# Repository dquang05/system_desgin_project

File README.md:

# ESP32 Autonomous Mobile Robot (AMR)

An advanced Autonomous Mobile Robot firmware built on the **ESP-IDF v5.x** framework. Designed with strict real-time constraints, thread-safety, and modular architecture, this project demonstrates professional-grade embedded systems engineering using **FreeRTOS** and Object-Oriented C++.

## 🚀 System Architecture

The firmware is designed with a strict **Application-Library Separation**.

- `lib/`: Contains hardware-agnostic, non-blocking drivers (Motor Control, PID, ADC DMA, Loadcell, Wi-Fi). No FreeRTOS tasks are spawned here.
- `src/`: The Application layer orchestrating high-level state machines, task creation, and global resource management.

### Key Engineering Highlights

- **Deterministic Real-Time Execution:** Motion control and PID loops run precisely at 100Hz in a pinned Core 1 task.
- **Thread Safety:** Lock-free passing where possible, combined with strict `portENTER_CRITICAL` Spinlocks for sharing high-frequency data (like Encoder ticks and ADC raw values) across multicore tasks.
- **Zero Dynamic Allocation in Critical Loops:** No `malloc` or `new` in polling loops. Memory is strictly stack-allocated or statically provisioned at startup to prevent Heap Fragmentation.
- **Direct Memory Access (DMA):** The 5-channel Infrared Line Sensor array is sampled at 20kHz continuously via ESP32's ADC DMA hardware, entirely offloading the CPU.

## 🧠 Control Algorithms

### 1. Velocity Control (Low-Level)

- **Incremental PID Controller:** Controls the TB6612 H-Bridge drivers coupled with Quadrature Encoders.
- **Slew Rate Limiting:** Prevents sudden current spikes (Back-EMF) by artificially capping the maximum acceleration `dv/dt`.
- **Integral Anti-Windup:** Prevents overshooting when wheels are mechanically jammed or lose traction.

### 2. Autonomous Navigation (High-Level)

- **Line Tracking:** Uses Weighted Average (Centroid) calculation with Affine Calibration to determine precise offset error (`e2`).
- **State Machine:** Seamlessly transitions between `MOVING_TO_PICKUP`, `WAITING_FOR_PACKAGE` (Loadcell integration), and `DELIVERING`.
- **Two-Phase Pivot Turn:** Executes precise turning maneuvers at intersections without the need for IMU/Compass, relying purely on encoder odometry and side-sensor polling.

### 3. Remote Telemetry & Tuning

- Utilizes asynchronous **UDP Sockets** to broadcast telemetry data (RPM, Duty Cycle, Sensor Arrays) to a local network at high frequency.
- Supports Live-Tuning: Send a JSON payload via UDP to dynamically update PID gains, steering RPMs, or loadcell thresholds **without recompiling or halting the robot**.

## 🛠️ Build & Flash Instructions

This project is configured using standard ESP-IDF CMake.

1. **Prerequisites:** Ensure ESP-IDF v5.x is installed.
2. **Set Target:**
   ```bash
   idf.py set-target esp32
   ```
3. **Build & Flash:**
   ```bash
   idf.py build
   idf.py -p PORT flash monitor
   ```

## 📁 Repository Structure

```text
├── MCU/
│   ├── include/           # Shared structures, Configs, and Orchestrator Headers
│   ├── src/               # FreeRTOS Tasks (Motion, Telemetry, UDP) & Main
│   ├── lib/               # Independent Component Libraries
│   │   ├── adc_dma/       # Continuous DMA ADC Driver
│   │   ├── loadcell_hx711/# HX711 Weight Sensor
│   │   ├── tb6612_encoder/# Motor & Quadrature Encoder Driver
│   │   ├── velocity_pid/  # Slew-Rate Limited PID
│   │   └── wifi_manager/  # Wi-Fi Station & AP provisioning
│   └── CMakeLists.txt     # Global IDF Component Registration
└── UI/                    # Node.js Server & Web Dashboard for UDP Telemetry
```

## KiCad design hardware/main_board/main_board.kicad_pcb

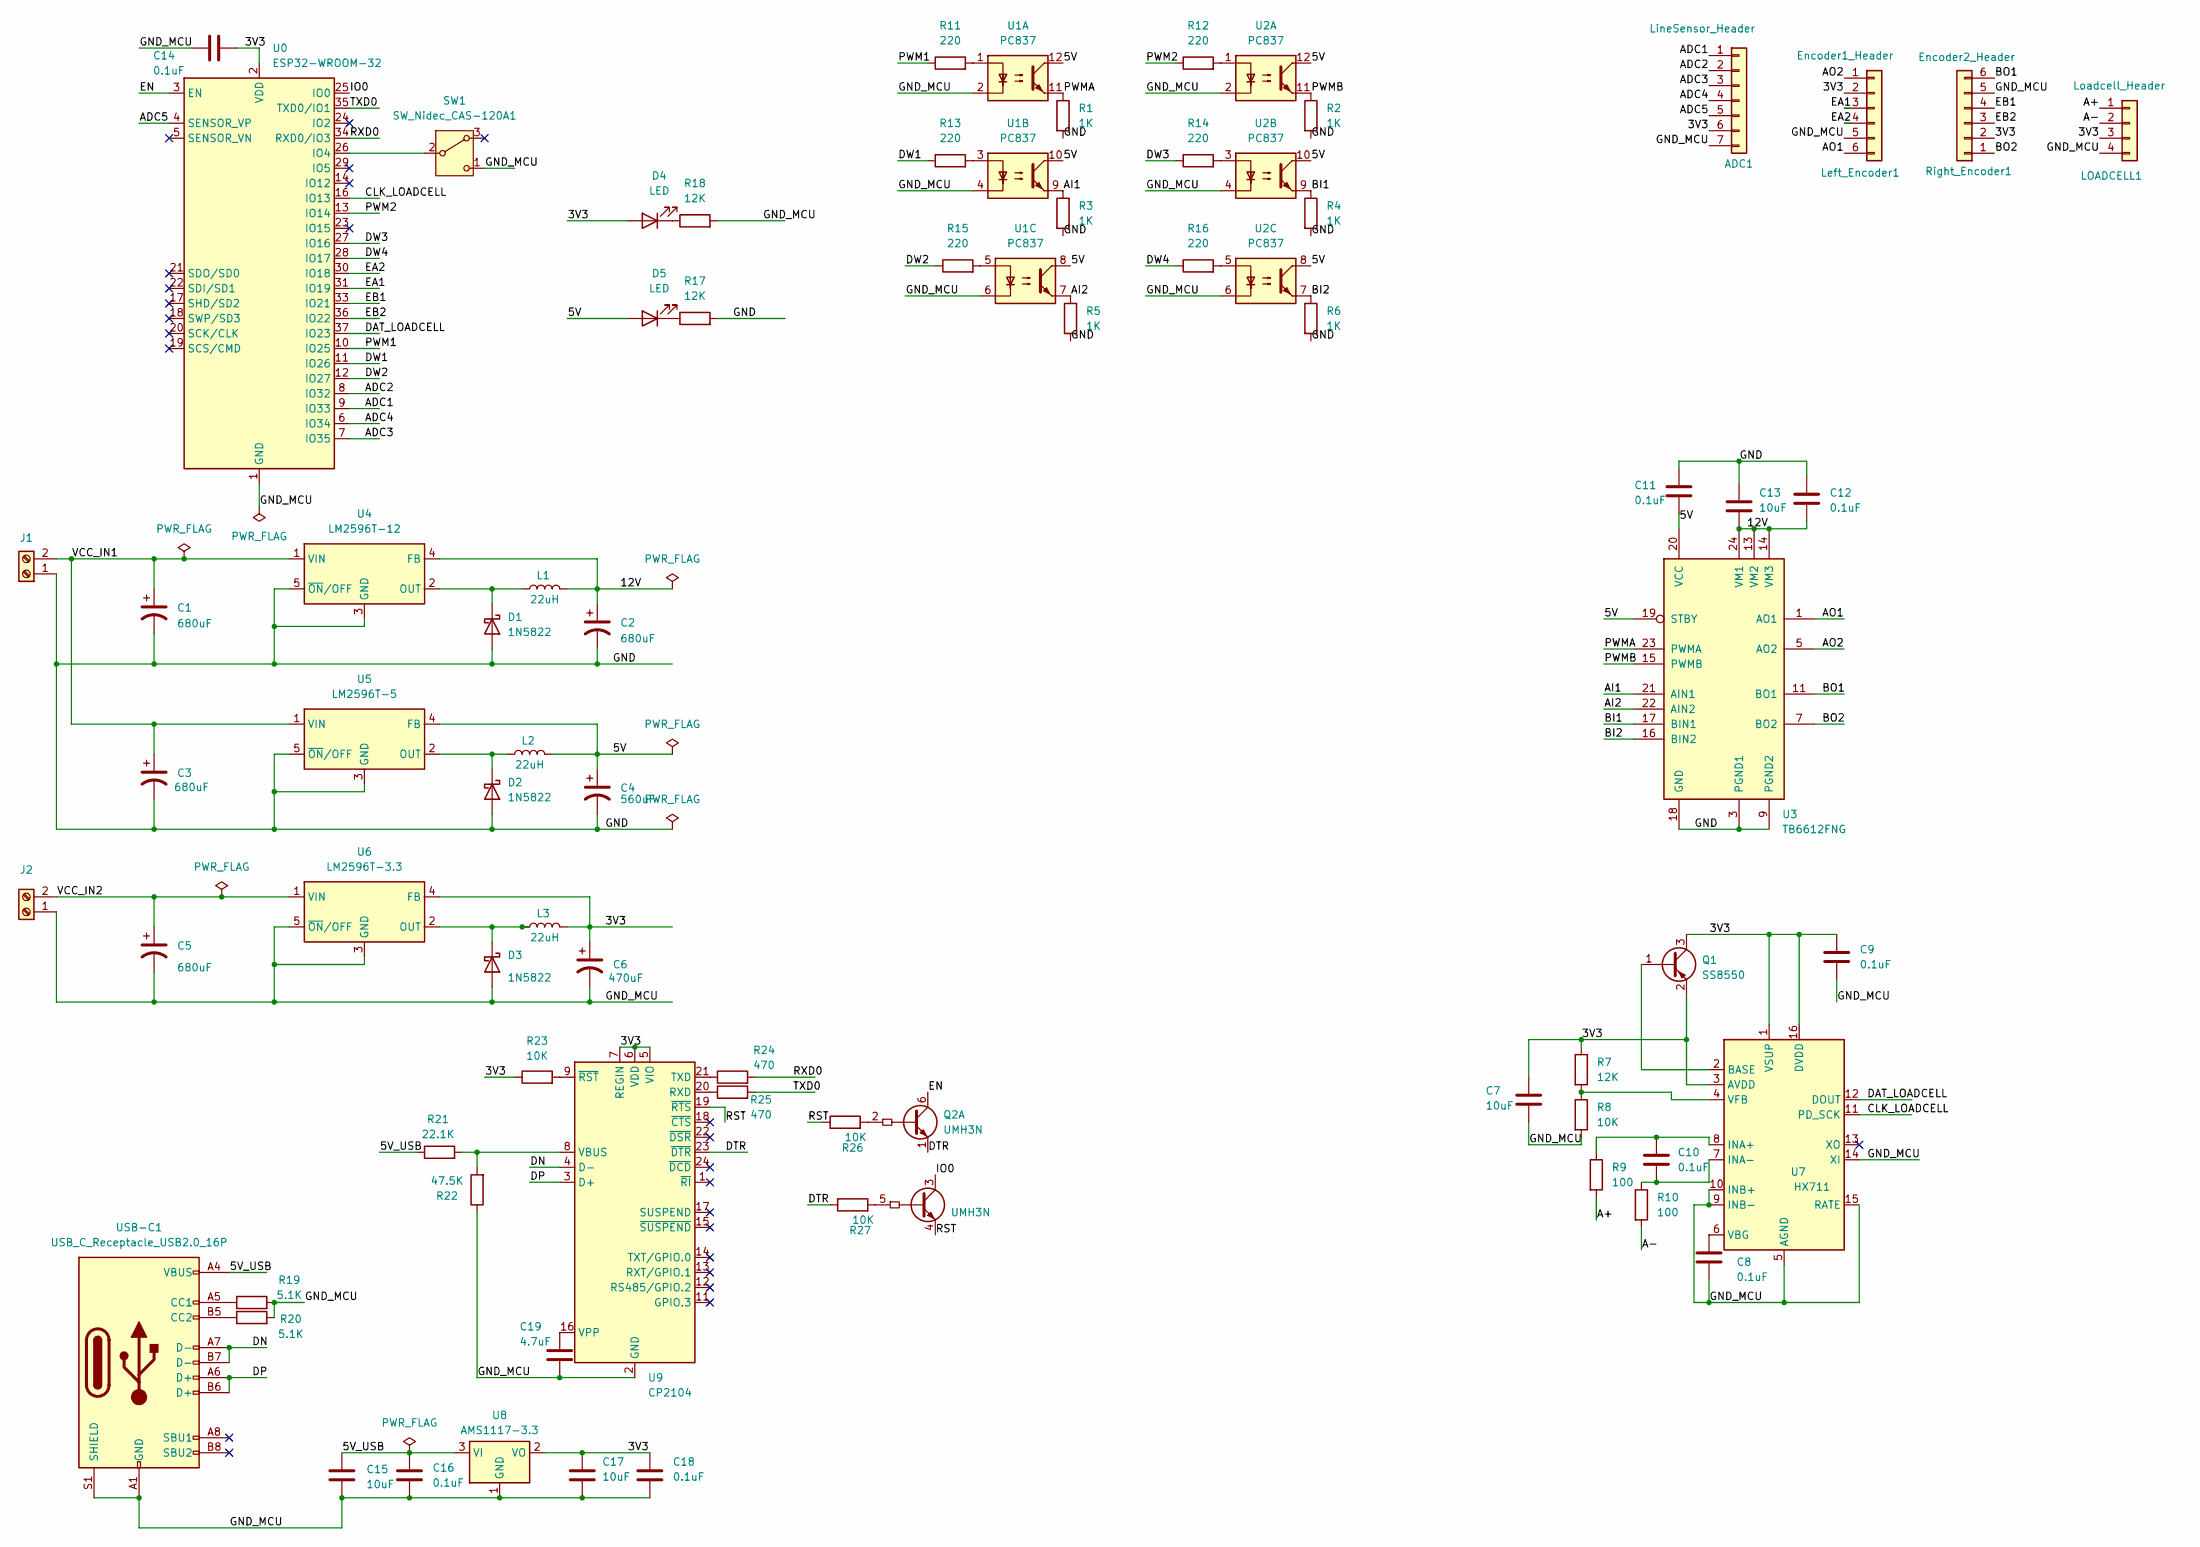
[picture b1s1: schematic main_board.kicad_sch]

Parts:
ADC1: LineSensor_Header; JST_EH_S7B-EH_1x07_P2.50mm_Horizontal
C1, C2, C3, C5: 680uF; CP_Radial_D8.0mm_P5.00mm
C4: 560uF; CP_Radial_D8.0mm_P5.00mm
C6: 470uF; CP_Radial_D8.0mm_P5.00mm
C7, C15, C17: 10uF; C_0805_2012Metric
C8, C9, C10, C11, C12, C14, C16, C18: 0.1uF; C_0805_2012Metric
C13: 10uF; C_1812_4532Metric_Pad1.57x3.40mm_HandSolder
C19: 4.7uF; C_0805_2012Metric
D1, D2, D3: 1N5822; D_0805_2012Metric
D4, D5: LED; LED_0805_2012Metric
J1: MCU POWER; TerminalBlock_bornier-2_P5.08mm
J2: MOTOR POWER; TerminalBlock_bornier-2_P5.08mm
L1, L2, L3: 22uH; L_6.3x6.3_H3
LOADCELL1: Loadcell_Header; JST_EH_S4B-EH_1x04_P2.50mm_Horizontal
Left_Encoder1: Encoder1_Header; JST_EH_S6B-EH_1x06_P2.50mm_Horizontal
Q1: SS8550; SOT-23
Q2: UMH3N; SOT-363_SC-70-6
R1, R2, R3, R4, R5, R6: 1K; R_0603_1608Metric
R7, R17, R18: 12K; R_0603_1608Metric
R8, R23, R26, R27: 10K; R_0603_1608Metric
R9, R10: 100; R_0603_1608Metric
R11, R12, R13, R14, R15, R16: 220; R_0603_1608Metric
R19, R20: 5.1K; R_0603_1608Metric
R21: 22.1K; R_0603_1608Metric
R22: 47.5K; R_0603_1608Metric
R24, R25: 470; R_0603_1608Metric
Right_Encoder1: Encoder2_Header; JST_EH_S6B-EH_1x06_P2.50mm_Horizontal
SW1: SW_Nidec_CAS-120A1; SW_DIP_SPSTx01_Slide_6.7x4.1mm_W6.73mm_P2.54mm_LowProfile_J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
U0: ESP32-WROOM-32
U1, U2: PC837; DIP-12_W7.62mm
U3: TB6612FNG; SSOP-24_5.3x8.2mm_P0.65mm
U4: LM2596T-12; TO-220-5_Vertical
U5: LM2596T-5; TO-220-5_Vertical
U6: LM2596T-3.3; TO-220-5_Vertical
U7: HX711; SOIC-16_3.9x9.9mm_P1.27mm
U8: AMS1117-3.3; SOT-223-3_TabPin2
U9: CP2104; QFN-24-1EP_4x4mm_P0.5mm_EP2.6x2.6mm
USB-C1: USB_C_Receptacle_USB2.0_16P; USB_C_Receptacle_GCT_USB4105-xx-A_16P_TopMnt_Horizontal

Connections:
/3V3: ADC1.6, C6.1, C7.1, C9.1, C14.1, C17.1, C18.1, D4.2 (A), L3.2, LOADCELL1.3, Left_Encoder1.2, Q1.2 (E), Q1.3 (C), R7.1, R23.1, Right_Encoder1.2, U0.2 (VDD), U6.4 (FB), U7.1 (VSUP), U7.3 (AVDD), U7.16 (DVDD), U8.2 (VO), U9.5 (VIO), U9.6 (VDD), U9.7 (REGIN)
/5V: C4.1, C11.2, D5.2 (A), L2.2, U1.8, U1.10, U1.12, U2.8, U2.10, U2.12, U3.19 (STBY), U3.20 (VCC), U5.4 (FB)
/5V_USB: C15.1, C16.1, R21.1, U8.3 (VI), USB-C1.A4 (VBUS), USB-C1.A9 (VBUS), USB-C1.B4 (VBUS), USB-C1.B9 (VBUS)
/12V: C2.1, C12.2, C13.2, L1.2, U3.13 (VM2), U3.14 (VM3), U3.24 (VM1), U4.4 (FB)
/A+: LOADCELL1.1, R9.2
/A-: LOADCELL1.2, R10.2
/ADC1: ADC1.1, U0.9 (IO33)
/ADC2: ADC1.2, U0.8 (IO32)
/ADC3: ADC1.3, U0.7 (IO35)
/ADC4: ADC1.4, U0.6 (IO34)
/ADC5: ADC1.5, U0.4 (SENSOR_VP)
/AI1: R3.1, U1.9, U3.21 (AIN1)
/AI2: R5.1, U1.7, U3.22 (AIN2)
/AO1: Left_Encoder1.6, U3.1 (AO1), U3.2 (AO1)
/AO2: Left_Encoder1.1, U3.5 (AO2), U3.6 (AO2)
/BI1: R4.1, U2.9, U3.17 (BIN1)
/BI2: R6.1, U2.7, U3.16 (BIN2)
/BO1: Right_Encoder1.6, U3.11 (BO1), U3.12 (BO1)
/BO2: Right_Encoder1.1, U3.7 (BO2), U3.8 (BO2)
/CLK_LOADCELL: U0.16 (IO13), U7.11 (PD_SCK)
/DAT_LOADCELL: U0.37 (IO23), U7.12 (DOUT)
/DN: U9.4 (D-), USB-C1.A7 (D-), USB-C1.B7 (D-)
/DP: U9.3 (D+), USB-C1.A6 (D+), USB-C1.B6 (D+)
/DTR: Q2.1 (E1), R27.1, U9.23 (~DTR)
/DW1: R13.1, U0.11 (IO26)
/DW2: R15.1, U0.12 (IO27)
/DW3: R14.1, U0.27 (IO16)
/DW4: R16.1, U0.28 (IO17)
/EA1: Left_Encoder1.3, U0.31 (IO19)
/EA2: Left_Encoder1.4, U0.30 (IO18)
/EB1: Right_Encoder1.4, U0.33 (IO21)
/EB2: Right_Encoder1.3, U0.36 (IO22)
/EN: Q2.6 (C1), U0.3 (EN)
/GND: C1.2, C2.2, C3.2, C4.2, C11.1, C12.1, C13.1, D1.2 (A), D2.2 (A), J1.1, R1.2, R2.2, R3.2, R4.2, R5.2, R6.2, R17.2, U3.3 (PGND1), U3.4 (PGND1), U3.9 (PGND2), U3.10 (PGND2), U3.18 (GND), U4.3 (GND), U4.5 (~ON/OFF), U5.3 (GND), U5.5 (~ON/OFF)
/GND_MCU: ADC1.7, C5.2, C6.2, C7.2, C8.2, C9.2, C14.2, C15.2, C16.2, C17.2, C18.2, C19.2, D3.2 (A), J2.1, LOADCELL1.4, Left_Encoder1.5, R8.2, R18.2, R19.2, R20.2, R22.1, Right_Encoder1.5, SW1.1 (C), U0.1 (GND), U0.15 (GND), U0.38 (GND), U0.39 (GND), U1.2, U1.4, U1.6, U2.2, U2.4, U2.6, U6.3 (GND), U6.5 (~ON/OFF), U7.5 (AGND), U7.9 (INB-), U7.10 (INB+), U7.14 (XI), U7.15 (RATE), U8.1 (GND), U9.2 (GND), U9.25 (GND), USB-C1.A1 (GND), USB-C1.A12 (GND), USB-C1.B1 (GND), USB-C1.B12 (GND), USB-C1.S1 (SHIELD)
/IO0: Q2.3 (C2), U0.25 (IO0)
/PWM1: R11.1, U0.10 (IO25)
/PWM2: R12.1, U0.13 (IO14)
/PWMA: R1.1, U1.11, U3.23 (PWMA)
/PWMB: R2.1, U2.11, U3.15 (PWMB)
/RST: Q2.4 (E2), R26.1, U9.19 (~RTS)
/RXD0: R24.2, U0.34 (RXD0/IO3)
/TXD0: R25.2, U0.35 (TXD0/IO1)
/VCC_IN1: C1.1, C3.1, J1.2, U4.1 (VIN), U5.1 (VIN)
/VCC_IN2: C5.1, J2.2, U6.1 (VIN)
unnamed: D1.1 (K), L1.1, U4.2 (OUT)
unnamed: D2.1 (K), L2.1, U5.2 (OUT)
unnamed: D3.1 (K), L3.1, U6.2 (OUT)
unnamed: D4.1 (K), R18.1
unnamed: D5.1 (K), R17.1
unnamed: Q1.1 (B), U7.2 (BASE)
unnamed: Q2.2 (B1), R26.2
unnamed: Q2.5 (B2), R27.2
unnamed: R11.2, U1.1
unnamed: R12.2, U2.1
unnamed: R13.2, U1.3
unnamed: R14.2, U2.3
unnamed: R15.2, U1.5
unnamed: R16.2, U2.5
unnamed: SW1.2 (B), U0.26 (IO4)
unnamed: C10.1, R9.1, U7.8 (INA+)
unnamed: C10.2, R10.1, U7.7 (INA-)
unnamed: C8.1, U7.6 (VBG)
unnamed: R7.2, R8.1, U7.4 (VFB)
unnamed: R25.1, U9.20 (RXD)
unnamed: R24.1, U9.21 (TXD)
unnamed: R21.2, R22.2, U9.8 (VBUS)
unnamed: C19.1, U9.16 (VPP)
unnamed: R23.2, U9.9 (~RST)
unnamed: R19.1, USB-C1.A5 (CC1)
unnamed: R20.1, USB-C1.B5 (CC2)

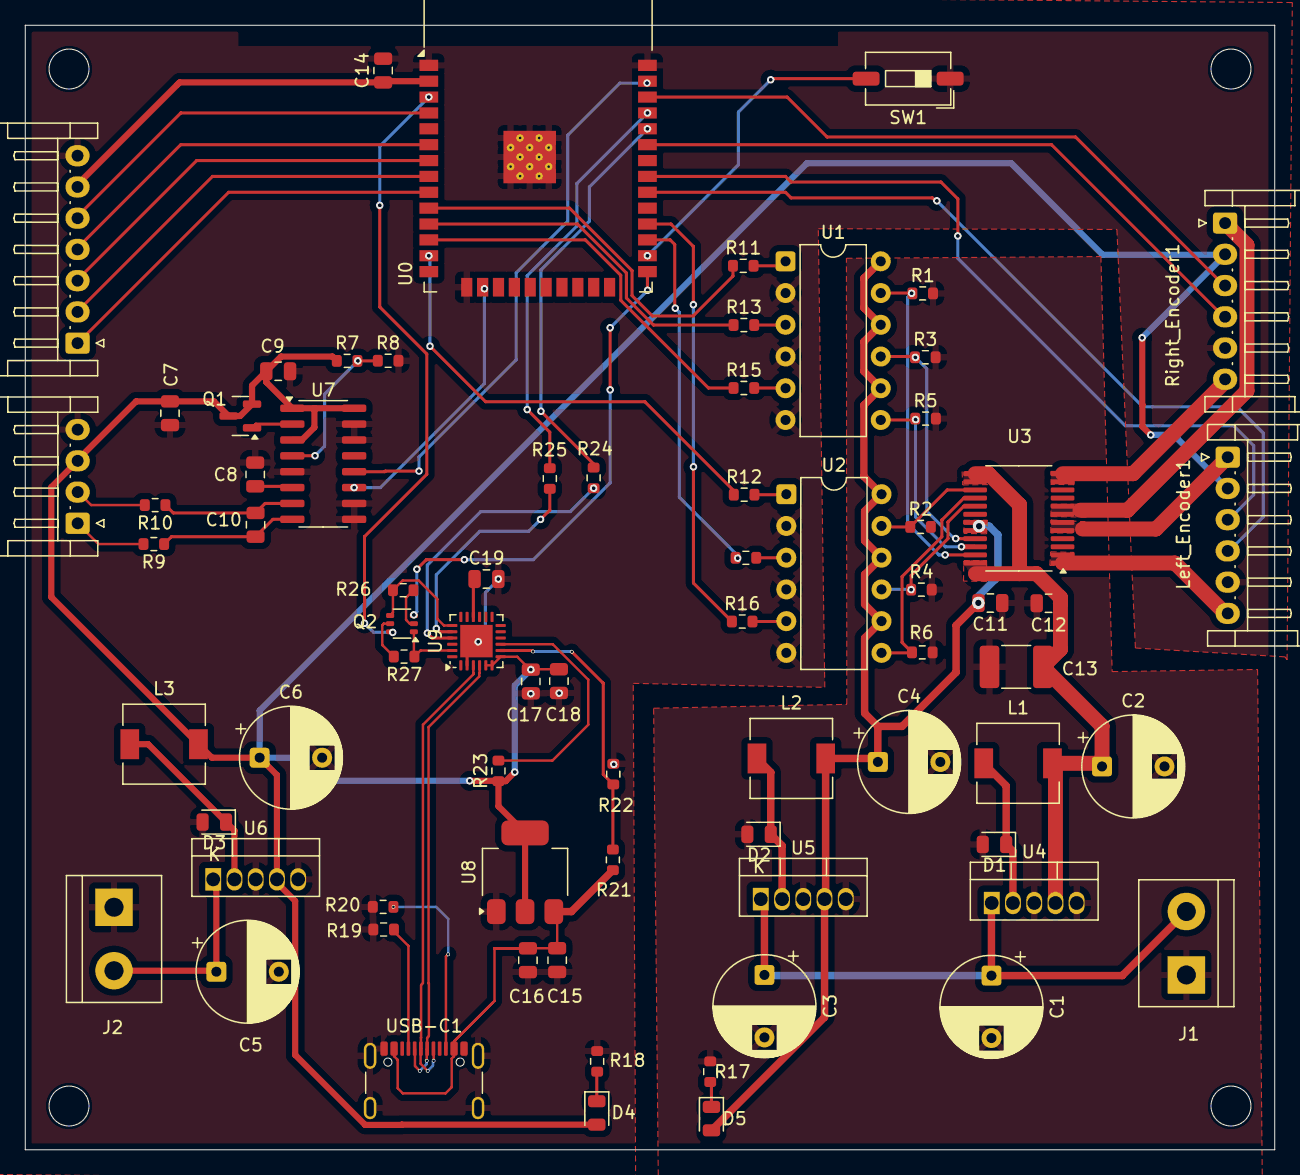
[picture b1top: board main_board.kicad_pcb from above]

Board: 2 copper layers, 100.0 x 90.0 mm, 74 parts (0 on the bottom side), 71 nets.

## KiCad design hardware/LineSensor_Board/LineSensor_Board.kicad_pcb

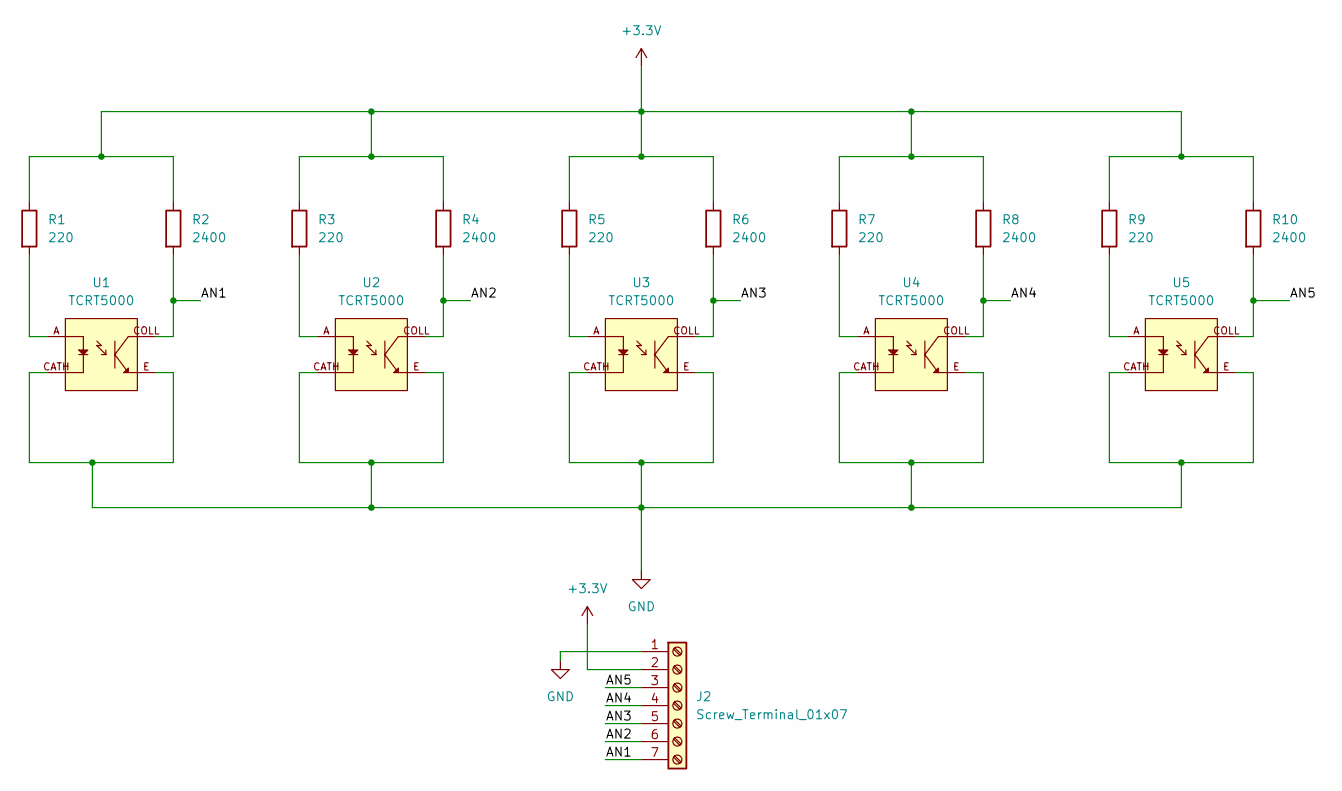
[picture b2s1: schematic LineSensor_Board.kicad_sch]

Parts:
J2: Screw_Terminal_01x07; PinHeader_1x07_P2.54mm_Vertical
R1, R3, R5, R7, R9: 220; R_Axial_DIN0207_L6.3mm_D2.5mm_P7.62mm_Horizontal
R2, R4, R6, R8, R10: 2400; R_Axial_DIN0207_L6.3mm_D2.5mm_P7.62mm_Horizontal
U1, U2, U3, U4, U5: TCRT5000; OPTO_TCRT5000; PARTREV 1.7

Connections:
+3.3V: J2.2, R1.1, R2.1, R3.1, R4.1, R5.1, R6.1, R7.1, R8.1, R9.1, R10.1
/AN1: J2.7, R2.2, U1.COLL
/AN2: J2.6, R4.2, U2.COLL
/AN3: J2.5, R6.2, U3.COLL
/AN4: J2.4, R8.2, U4.COLL
/AN5: J2.3, R10.2, U5.COLL
GND: J2.1, U1.CATH, U1.E, U2.CATH, U2.E, U3.CATH, U3.E, U4.CATH, U4.E, U5.CATH, U5.E
unnamed: R1.2, U1.A
unnamed: R3.2, U2.A
unnamed: R5.2, U3.A
unnamed: R7.2, U4.A
unnamed: R9.2, U5.A

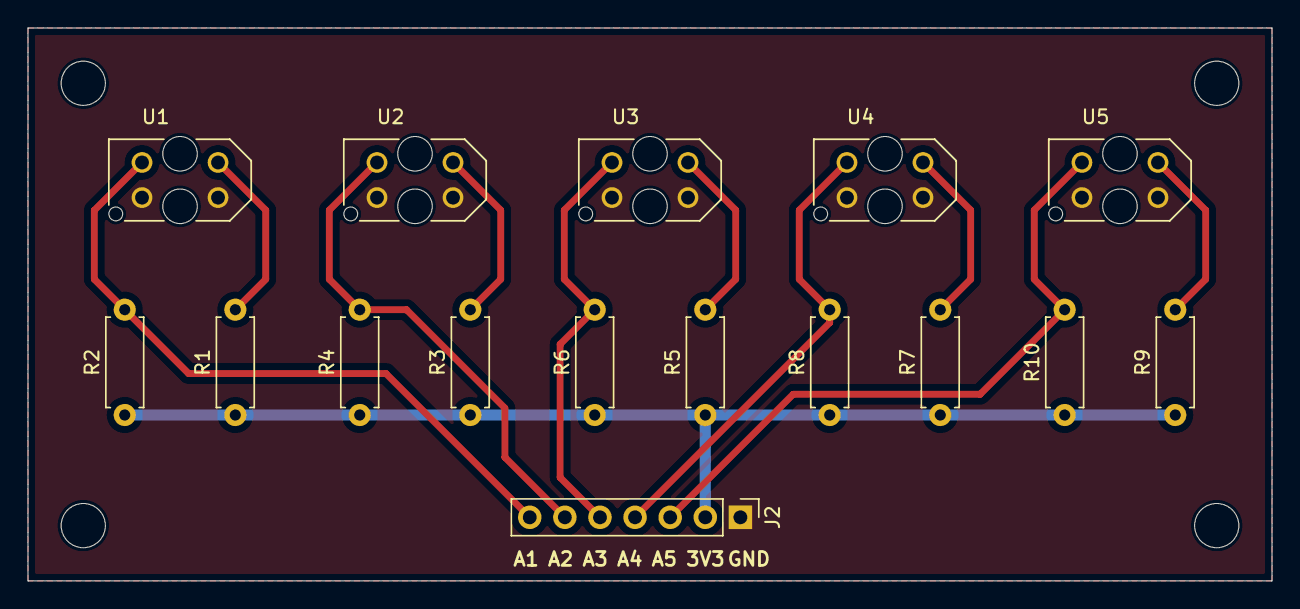
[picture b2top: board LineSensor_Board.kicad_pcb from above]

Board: 2 copper layers, 90.0 x 40.0 mm, 16 parts (0 on the bottom side), 12 nets.

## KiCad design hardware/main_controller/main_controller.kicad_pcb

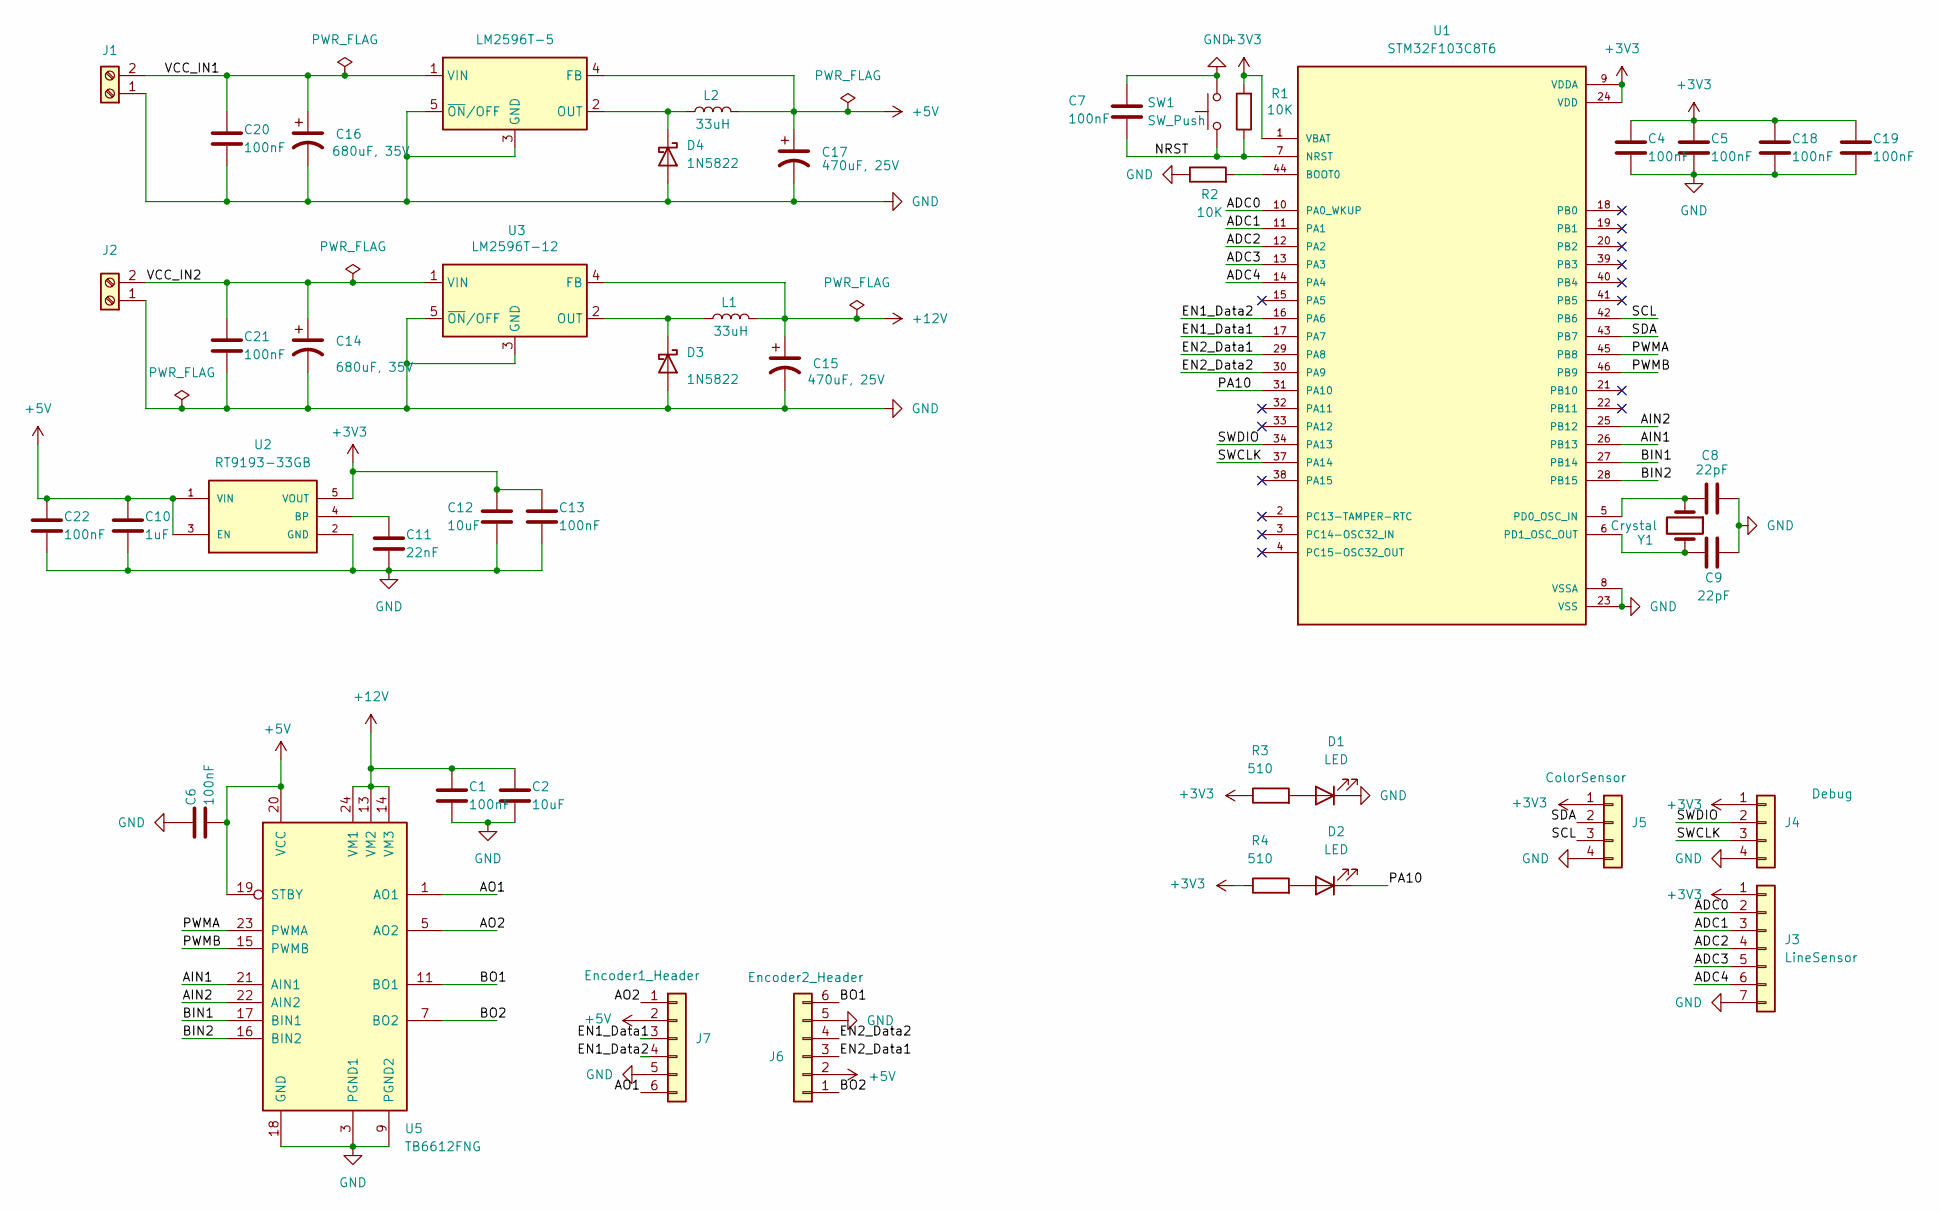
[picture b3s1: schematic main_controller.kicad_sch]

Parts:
C1, C4, C5, C6, C7, C13, C18, C19, C20, C21, C22: 100nF; C_0805_2012Metric_Pad1.18x1.45mm_HandSolder
C2, C12: 10uF; C_0805_2012Metric_Pad1.18x1.45mm_HandSolder
C8, C9: 22pF; C_0805_2012Metric_Pad1.18x1.45mm_HandSolder
C10: 1uF; C_0805_2012Metric_Pad1.18x1.45mm_HandSolder
C11: 22nF; C_0805_2012Metric_Pad1.18x1.45mm_HandSolder
C14, C16: 680uF, 35V; CP_Radial_D8.0mm_P5.00mm
C15, C17: 470uF, 25V; CP_Radial_D8.0mm_P5.00mm
D1, D2: LED; LED_0805_2012Metric_Pad1.15x1.40mm_HandSolder
D3, D4: 1N5822; D_DO-201AD_P15.24mm_Horizontal
J1: MCU POWER; TerminalBlock_bornier-2_P5.08mm
J2: MOTOR POWER; TerminalBlock_bornier-2_P5.08mm
J3: LineSensor; PinHeader_1x07_P2.54mm_Vertical
J4: Debug; PinHeader_1x04_P2.54mm_Vertical
J5: ColorSensor; PinHeader_1x04_P2.54mm_Vertical
J6: Encoder2_Header; PinHeader_1x06_P2.54mm_Vertical
J7: Encoder1_Header; PinHeader_1x06_P2.54mm_Vertical
L1, L2: 33uH; L_Radial_D10.0mm_P5.00mm_Fastron_07P
R1, R2: 10K; R_0603_1608Metric_Pad0.98x0.95mm_HandSolder
R3, R4: 510; R_0603_1608Metric_Pad0.98x0.95mm_HandSolder
SW1: SW_Push; SW_SPST_PTS647_Sx38
U1: STM32F103C8T6; QFP50P900X900X160-48N; PARTREV 10
U2: RT9193-33GB; SOT94P279X129-5N
U3: LM2596T-12; TO-220-5_Vertical
U4: LM2596T-5; TO-220-5_Vertical
U5: TB6612FNG; SSOP-24_5.3x8.2mm_P0.65mm
Y1: Crystal; Crystal_SMD_5032-2Pin_5.0x3.2mm_HandSoldering

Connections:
+3V3: C4.1, C5.1, C12.1, C13.1, C18.1, C19.1, J3.1, J4.1, J5.1, R1.2, R3.1, R4.1, U1.1 (VBAT), U1.9 (VDDA), U1.24 (VDD), U1.36 (VDD), U1.48 (VDD), U2.5 (VOUT)
+5V: C6.2, C10.1, C17.1, C22.1, J6.2, J7.2, L2.2, U2.1 (VIN), U2.3 (EN), U4.4 (FB), U5.19 (STBY), U5.20 (VCC)
+12V: C1.1, C2.1, C15.1, L1.2, U3.4 (FB), U5.13 (VM2), U5.14 (VM3), U5.24 (VM1)
/ADC0: J3.2, U1.10 (PA0_WKUP)
/ADC1: J3.3, U1.11 (PA1)
/ADC2: J3.4, U1.12 (PA2)
/ADC3: J3.5, U1.13 (PA3)
/ADC4: J3.6, U1.14 (PA4)
/AIN1: U1.26 (PB13), U5.21 (AIN1)
/AIN2: U1.25 (PB12), U5.22 (AIN2)
/AO1: J7.6, U5.1 (AO1), U5.2 (AO1)
/AO2: J7.1, U5.5 (AO2), U5.6 (AO2)
/BIN1: U1.27 (PB14), U5.17 (BIN1)
/BIN2: U1.28 (PB15), U5.16 (BIN2)
/BO1: J6.6, U5.11 (BO1), U5.12 (BO1)
/BO2: J6.1, U5.7 (BO2), U5.8 (BO2)
/EN1_Data1: J7.3, U1.17 (PA7)
/EN1_Data2: J7.4, U1.16 (PA6)
/EN2_Data1: J6.3, U1.29 (PA8)
/EN2_Data2: J6.4, U1.30 (PA9)
/NRST: C7.2, R1.1, SW1.1, U1.7 (NRST)
/PA10: D2.1 (K), U1.31 (PA10)
/PWMA: U1.45 (PB8), U5.23 (PWMA)
/PWMB: U1.46 (PB9), U5.15 (PWMB)
/SCL: J5.3, U1.42 (PB6)
/SDA: J5.2, U1.43 (PB7)
/SWCLK: J4.3, U1.37 (PA14)
/SWDIO: J4.2, U1.34 (PA13)
/VCC_IN1: C16.1, C20.1, J1.2, U4.1 (VIN)
/VCC_IN2: C14.1, C21.1, J2.2, U3.1 (VIN)
GND: C1.2, C2.2, C4.2, C5.2, C6.1, C7.1, C8.1, C9.1, C10.2, C11.2, C12.2, C13.2, C14.2, C15.2, C16.2, C17.2, C18.2, C19.2, C20.2, C21.2, C22.2, D1.1 (K), D3.2 (A), D4.2 (A), J1.1, J2.1, J3.7, J4.4, J5.4, J6.5, J7.5, R2.1, SW1.2, U1.8 (VSSA), U1.23 (VSS), U1.35 (VSS), U1.47 (VSS), U2.2 (GND), U3.3 (GND), U3.5 (~ON/OFF), U4.3 (GND), U4.5 (~ON/OFF), U5.3 (PGND1), U5.4 (PGND1), U5.9 (PGND2), U5.10 (PGND2), U5.18 (GND)
unnamed: D1.2 (A), R3.2
unnamed: D2.2 (A), R4.2
unnamed: D3.1 (K), L1.1, U3.2 (OUT)
unnamed: D4.1 (K), L2.1, U4.2 (OUT)
unnamed: R2.2, U1.44 (BOOT0)
unnamed: C8.2, U1.5 (PD0_OSC_IN), Y1.1
unnamed: C9.2, U1.6 (PD1_OSC_OUT), Y1.2
unnamed: C11.1, U2.4 (BP)

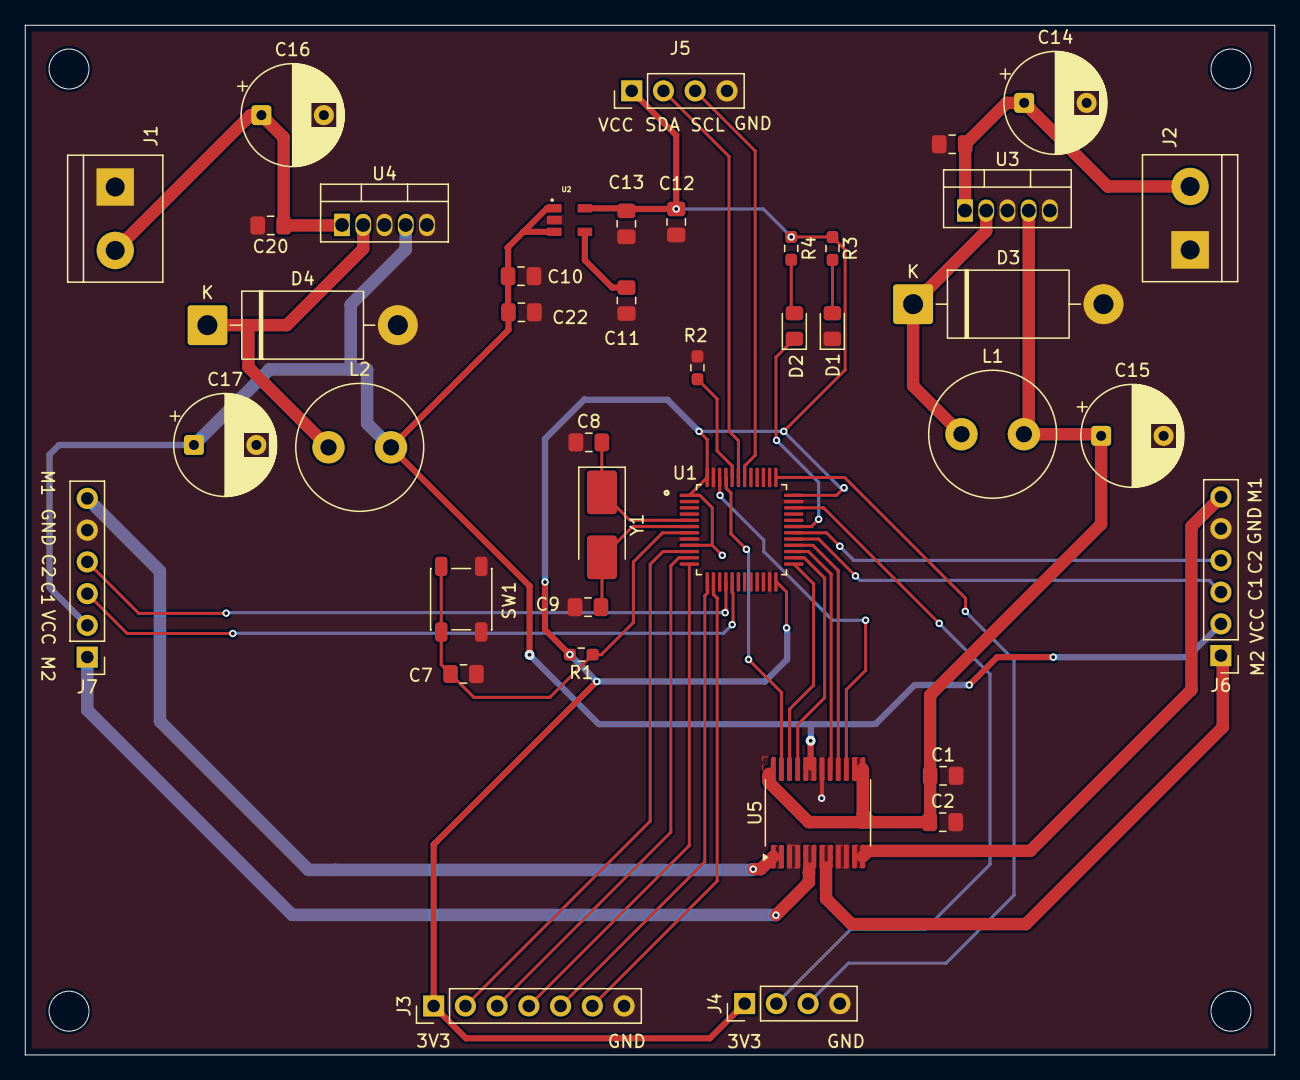
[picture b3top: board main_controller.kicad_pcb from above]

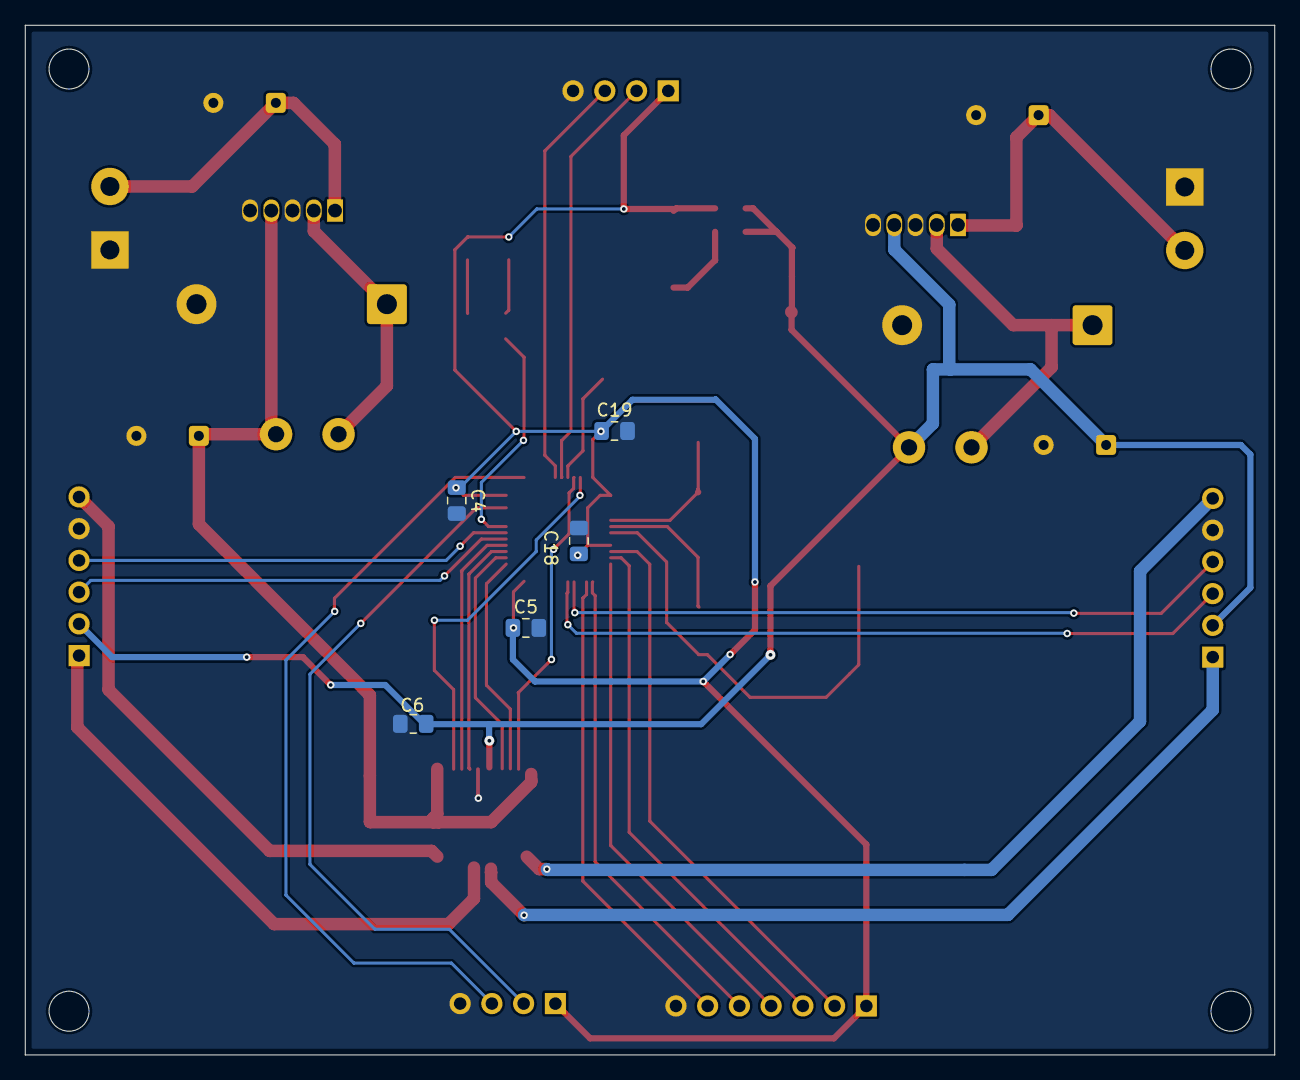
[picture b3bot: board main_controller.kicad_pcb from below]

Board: 2 copper layers, 100.0 x 82.4 mm, 45 parts (5 on the bottom side), 39 nets.

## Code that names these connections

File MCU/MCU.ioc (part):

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Mcu.Name=STM32F103C(8-B)Tx
Mcu.Package=LQFP48
Mcu.UserName=STM32F103C8Tx
PA1.GPIOParameters=GPIO_Label
PA1.GPIO_Label=LINE_SENSOR_1
PA1.Signal=ADCx_IN1
PA10.Signal=GPIO_Output
PA11.Signal=GPIO_Output
PA13.Mode=Serial_Wire
PA13.Signal=SYS_JTMS-SWDIO
PA14.Mode=Serial_Wire
PA14.Signal=SYS_JTCK-SWCLK
PA15.Signal=S_TIM2_CH1_ETR
PA2.GPIOParameters=GPIO_Label
PA2.GPIO_Label=LINE_SENSOR_2
PA2.Signal=ADCx_IN2
PA3.GPIOParameters=GPIO_Label
PA3.GPIO_Label=LINE_SENSOR_3
PA3.Signal=ADCx_IN3
PA4.GPIOParameters=GPIO_Label
PA4.GPIO_Label=LINE_SENSOR_4
PA4.Signal=ADCx_IN4
PA5.GPIOParameters=GPIO_Label
PA5.GPIO_Label=LINE_SENSOR_5
PA5.Signal=ADCx_IN5
PA6.Signal=S_TIM3_CH1
PA7.Signal=S_TIM3_CH2
PA8.Signal=GPIO_Output
PA9.Signal=GPIO_Output
PB3.Signal=S_TIM2_CH2
PB6.Signal=S_TIM4_CH1
PB7.Signal=S_TIM4_CH2
board=custom

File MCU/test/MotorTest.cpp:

/**
 * @file MotorTest.cpp
 * @brief Test for TB6612 Motor & Encoder Driver
 *
 * =========================================================================
 * PHYSICAL WIRING GUIDE (ESP32 -> TB6612 -> Motor with Encoder):
 * =========================================================================
 * [ESP32 Pin]      [TB6612 Pin]     [Motor / Encoder]
 * -------------------------------------------------------------------------
 * GPIO 14   -----> PWMA             -
 * GPIO 26   -----> AIN1             -
 * GPIO 27   -----> AIN2             -
 *
 * GPIO 34   <----- -                Encoder Phase A (e.g. Yellow Wire)
 * GPIO 35   <----- -                Encoder Phase B (e.g. Green Wire)
 *
 * 3.3V      -----> VCC (Logic)      Encoder VCC (e.g. Blue or Red Wire)
 * VMOTOR    -----> VM (Motor Pwr)   -
 * GND       -----> GND              Encoder GND (e.g. Black Wire)
 *
 * -         -----> AO1              Motor Terminal + (Red)
 * -         -----> AO2              Motor Terminal - (Black)
 * =========================================================================
 * Note: GPIO 34, 35 are input-only pins, perfect for encoder reading.
 */

#include "../lib/tb6612_encoder/tb6612_encoder.hpp"
#include "esp_log.h"
#include "esp_timer.h"
#include "freertos/FreeRTOS.h"
#include "freertos/task.h"
#include <unity.h>

static const char *TAG = "MOTOR_TEST";

void test_motor_forward_backward_and_encoder_read() {
  Tb6612Encoder motor;

  tb6612_config_t config = {
      .pwm_gpio = 14,
      .in1_gpio = 26,
      .in2_gpio = 27,
      .enc_a_gpio = 34,
      .enc_b_gpio = 35,
      .pwm_freq_hz = 20000,
      .encoder_ppr =
          341, // Example: 341 PPR. Please update to match your specific motor!
      .pcnt_high_limit = 30000,
      .pcnt_low_limit = -30000};

  ESP_LOGI(TAG, "Initializing TB6612 motor driver...");
  esp_err_t err = motor.init(config);
  TEST_ASSERT_EQUAL(ESP_OK, err);

  ESP_LOGI(TAG, "Motor initialized. Running FORWARD at 50%% duty cycle...");
  motor.set_duty_cycle(50.0f);

  int64_t fwd_last_pulses = 0;
  int64_t fwd_last_time = esp_timer_get_time();
  motor.get_pulse_count(fwd_last_pulses);

  // Read values for 3 seconds
  for (int i = 0; i < 30; i++) {
    vTaskDelay(pdMS_TO_TICKS(100)); // 10Hz polling

    int64_t current_pulses = 0;
    float current_rpm = 0.0f;
    int64_t current_time = esp_timer_get_time();

    motor.get_pulse_count(current_pulses);
    motor.get_current_rpm(current_pulses, fwd_last_pulses,
                          current_time - fwd_last_time, current_rpm);

    ESP_LOGI(TAG, "[FWD | Duty: 50%%] Pulses: %lld | RPM: %.2f", current_pulses,
             current_rpm);

    fwd_last_pulses = current_pulses;
    fwd_last_time = current_time;
  }

  ESP_LOGI(TAG, "Stopping motor...");
  motor.set_duty_cycle(0.0f);
  vTaskDelay(pdMS_TO_TICKS(1000));

  ESP_LOGI(TAG, "Running BACKWARD at -30%% duty cycle...");
  motor.set_duty_cycle(-30.0f);

  int64_t bwd_last_pulses = 0;
  int64_t bwd_last_time = esp_timer_get_time();
  motor.get_pulse_count(bwd_last_pulses);

  // Read values for 3 seconds
  for (int i = 0; i < 30; i++) {
    vTaskDelay(pdMS_TO_TICKS(100)); // 10Hz polling

    int64_t current_pulses = 0;
    float current_rpm = 0.0f;
    int64_t current_time = esp_timer_get_time();

    motor.get_pulse_count(current_pulses);
    motor.get_current_rpm(current_pulses, bwd_last_pulses,
                          current_time - bwd_last_time, current_rpm);

    ESP_LOGI(TAG, "[BWD | Duty: -30%%] Pulses: %lld | RPM: %.2f",
             current_pulses, current_rpm);

    bwd_last_pulses = current_pulses;
    bwd_last_time = current_time;
  }

  ESP_LOGI(TAG, "Stopping and de-initializing motor...");
  motor.set_duty_cycle(0.0f);
}

// Required entry point for PlatformIO testing
extern "C" void app_main() {
  // Short delay to allow Serial Monitor to connect and capture early logs
  vTaskDelay(pdMS_TO_TICKS(2000));

  UNITY_BEGIN();
  RUN_TEST(test_motor_forward_backward_and_encoder_read);
  UNITY_END();
}

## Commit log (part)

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2026-06-20 Initial commit: Project initialization for AGV line follower
2026-06-22 hardware: PCB_demo complete
2026-06-25 chore(setup): init stm32 workspace
2026-06-27 refactor(mcu): migrate firmware project from STM32 to ESP32
2026-06-28 feat(wifi): implement Wi-Fi connectivity for MCU and setup log receiver service
2026-06-28 feat: implement motion_control loop
2026-06-30 fix: change ESP_ERR_CHECK to return esp_err_t for more robust
2026-06-30 feat: implement telemetry for logging data to UI, update UI for drawing ADC
